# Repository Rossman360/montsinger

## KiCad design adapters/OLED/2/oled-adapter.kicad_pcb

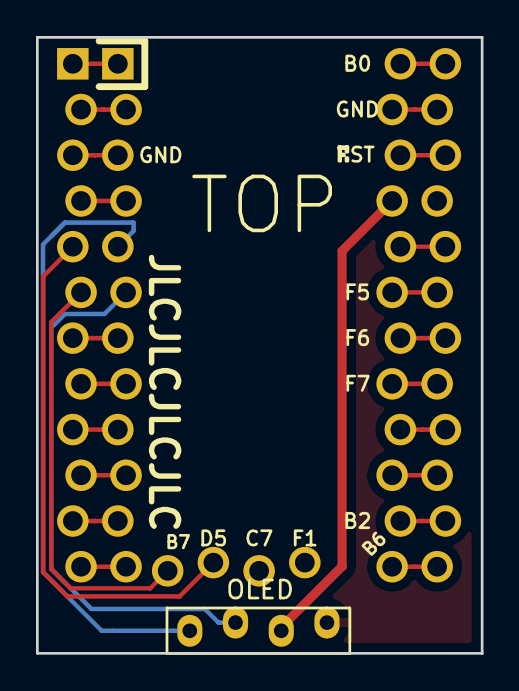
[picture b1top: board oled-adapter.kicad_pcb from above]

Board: 2 copper layers, 24.7 x 34.2 mm, 3 parts (0 on the bottom side), 26 nets.

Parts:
J1: OLED; OLED_1side
U1: ProMicro; Elite-C-ZigZag
U2: ProMicro; ArduinoProMicro-Mini-USB-ZigZag

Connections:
GND: J1.4, U1.23
unnamed: U1.1, U2.1
unnamed: U1.2, U2.2
unnamed: U1.3, U2.3
unnamed: U1.4, U2.4
unnamed: U1.7, U2.7
unnamed: U1.8, U2.8
unnamed: U1.9, U2.9
unnamed: U1.10, U2.10
unnamed: U1.11, U2.11
unnamed: U1.12, U2.12
unnamed: U1.13, U2.13
unnamed: U1.14, U2.14
unnamed: U1.15, U2.15
unnamed: U1.16, U2.16
unnamed: U1.17, U2.17
unnamed: U1.18, U2.18
unnamed: U1.19, U2.19
unnamed: U1.20, U2.20
unnamed: U1.22, U2.22
unnamed: U1.24, U2.24
unnamed: U1.25, U2.6
unnamed: U1.26, U2.5
SCL: J1.2, U1.6
SDA: J1.1, U1.5
VCC: J1.3, U1.21

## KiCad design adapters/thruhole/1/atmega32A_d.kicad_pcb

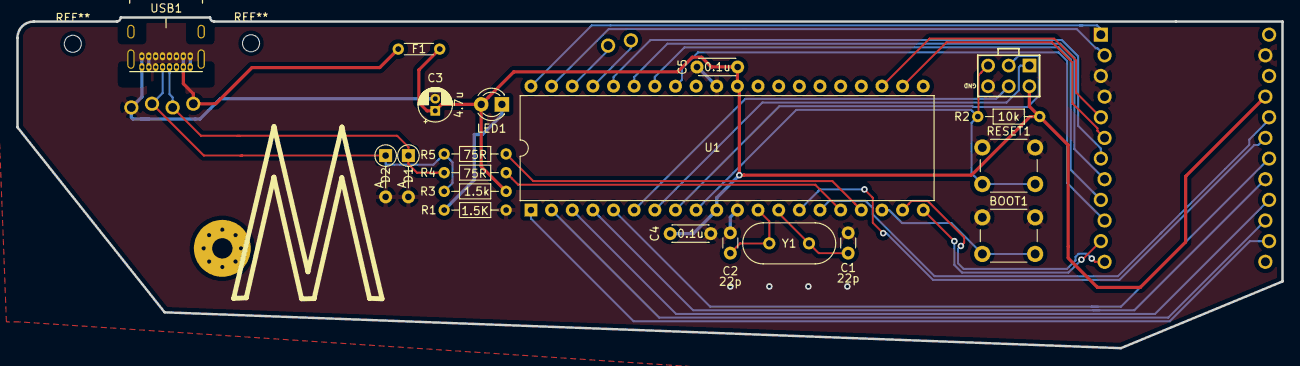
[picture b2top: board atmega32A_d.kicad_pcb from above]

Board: 2 copper layers, 155.6 x 40.7 mm, 23 parts (0 on the bottom side), 34 nets.

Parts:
BOOT1: BOOT; SW_PUSH_6mm
C1, C2: 22p; C_Disc_D3.0mm_W1.6mm_P2.50mm
C3: 4.7u; CP_Radial_D4.0mm_P1.50mm
C4, C5: 0.1u; C_Disc_D4.3mm_W1.9mm_P5.00mm
D1, D2: 3.6V; D_DO-35_SOD27_P5.08mm_Vertical_AnodeUp
F1: 500mA; polyfuse_5.1mm
J1: AVR-ISP-6; AVR_ICSP_3x2
J6: PA3; SinglePad
J6#2: PA2; SinglePad
LED1: POWER; LED_D3.0mm
R1: 1.5K; R_Axial_DIN0204_L3.6mm_D1.6mm_P7.62mm_Horizontal
R2: 10k; R_Axial_DIN0204_L3.6mm_D1.6mm_P7.62mm_Horizontal
R3: 1.5k; R_Axial_DIN0204_L3.6mm_D1.6mm_P7.62mm_Horizontal
R4, R5: 75R; R_Axial_DIN0204_L3.6mm_D1.6mm_P7.62mm_Horizontal
RESET1: RESET; SW_PUSH_6mm
U1: ATmega32A-PU; DIP-40_W15.24mm
U2: ProMicro; ArduinoProMicro-Mini-USB-ZigZag
USB1: USB_C_GCT_USB4085
Y1: Crystal; Crystal_HC49-4H_Vertical

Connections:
+5V: C3.1, C4.1, C5.1, F1.2, J1.2, LED1.2, R2.1, R3.2, U1.10, U1.30, U2.21, USB1.A9, USB1.B4
D+: R4.1, U1.16
D-: R5.1, U1.17
GND: BOOT1.1, C1.2, C2.2, C3.2, C4.2, C5.2, D1.2, D2.2, J1.6, R1.2, RESET1.1, U1.11, U1.31, U2.3, U2.4, U2.23, USB1.A12, USB1.B1
MISO: J1.1, U1.7
MOSI: J1.4, U1.6
unnamed: C1.1, U1.13, Y1.2
unnamed: C2.1, U1.12, Y1.1
unnamed: D1.1, R4.2, USB1.A6, USB1.B6
unnamed: D2.1, R3.1, R5.2, USB1.A7, USB1.B7
unnamed: F1.1, USB1.A4, USB1.B9
unnamed: LED1.1, R1.1
unnamed: U1.22, U2.6
unnamed: U1.23, U2.5
PA0: U1.40, U2.1
PA1: U1.39, U2.2
PA2: J6#2.1, U1.38
PA3: J6.1, U1.37
PA4: U1.36, U2.7
PA5: U1.35, U2.8
PA6: U1.34, U2.9
PA7: U1.33, U2.10
PB0: U1.1, U2.14
PB1: U1.2, U2.15
PB2: U1.3, U2.16
PB3: U1.4, U2.17
PB4: U1.5, U2.18
PD0: U1.14, U2.19
PD1: U1.15, U2.20
PD5: U1.19, U2.12
PD6: U1.20, U2.11
SCK: J1.3, U1.8
boot: BOOT1.2, U1.18
reset: J1.5, R2.2, RESET1.2, U1.9

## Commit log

2020-06-26 adding logos
2020-06-28 rbr4
2020-06-28 horizontal
2020-06-28 more
2020-07-03 adding adapters
